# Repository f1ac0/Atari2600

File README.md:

# Atari2600
Inside the lot I bought to get my first C64 was also and Atari 2600. It was also listed as "Untested", and it was obviously salvaged from a flood considering the mud and rust that was inside the case. It came without any game or accessory.

While waiting for the system to dry after a complete clean and rust removal I found the useful projects below to help me start with this system I didn't know anything about.
- First I needed some game so I put together a ROM cartridge on a breadboard and created a PCB from it.
- Then not a single TV receiver I had could tune the video and audio signals correctly, but a BT848 PCTV PCI card. The mod by Eddy Foucault worked perfectly, I made my own version with CMS components and 5v only.
- At last I removed the regulator to power the console from a modern 5V power source.

In this repository are the PCBs I created or modified for my own needs.

# Disclaimer and Acknowledgements
This is a hobbyist project, it comes with no warranty and no support. Also remember that the 40 years old hardware may fail because of such expansions.

I publish my work under the CC-BY-NC-SA license, unless stated otherwise. Thanks to everyone who share their knowledge and creations.

# Useful links

## Cartridge
- https://github.com/sarweiler/a2k6-cart
- https://github.com/robinhedwards/UnoCart-2600
- https://github.com/DirtyHairy/UnoCart-2600/releases
- https://github.com/rglenn/unocart2600-pcb
- https://github.com/Al-Nafuur/United-Carts-of-Atari

## Video SECAM Atari 2600 to RGB SCART TV
- http://eddystoys.blogspot.com/2014/08/atari-2600.html

## Video SECAM to PAL
- https://forums.atariage.com/topic/245189-converting-a-secam-atari-2600-to-pal-or-ntsc/

## Video PAL/NTSC to composite
- https://www.arcticretro.com/2021/03/27/atari-2600-composite-video-mod/
- https://www.instructables.com/ATARI-2600-Video-Composite-mod/

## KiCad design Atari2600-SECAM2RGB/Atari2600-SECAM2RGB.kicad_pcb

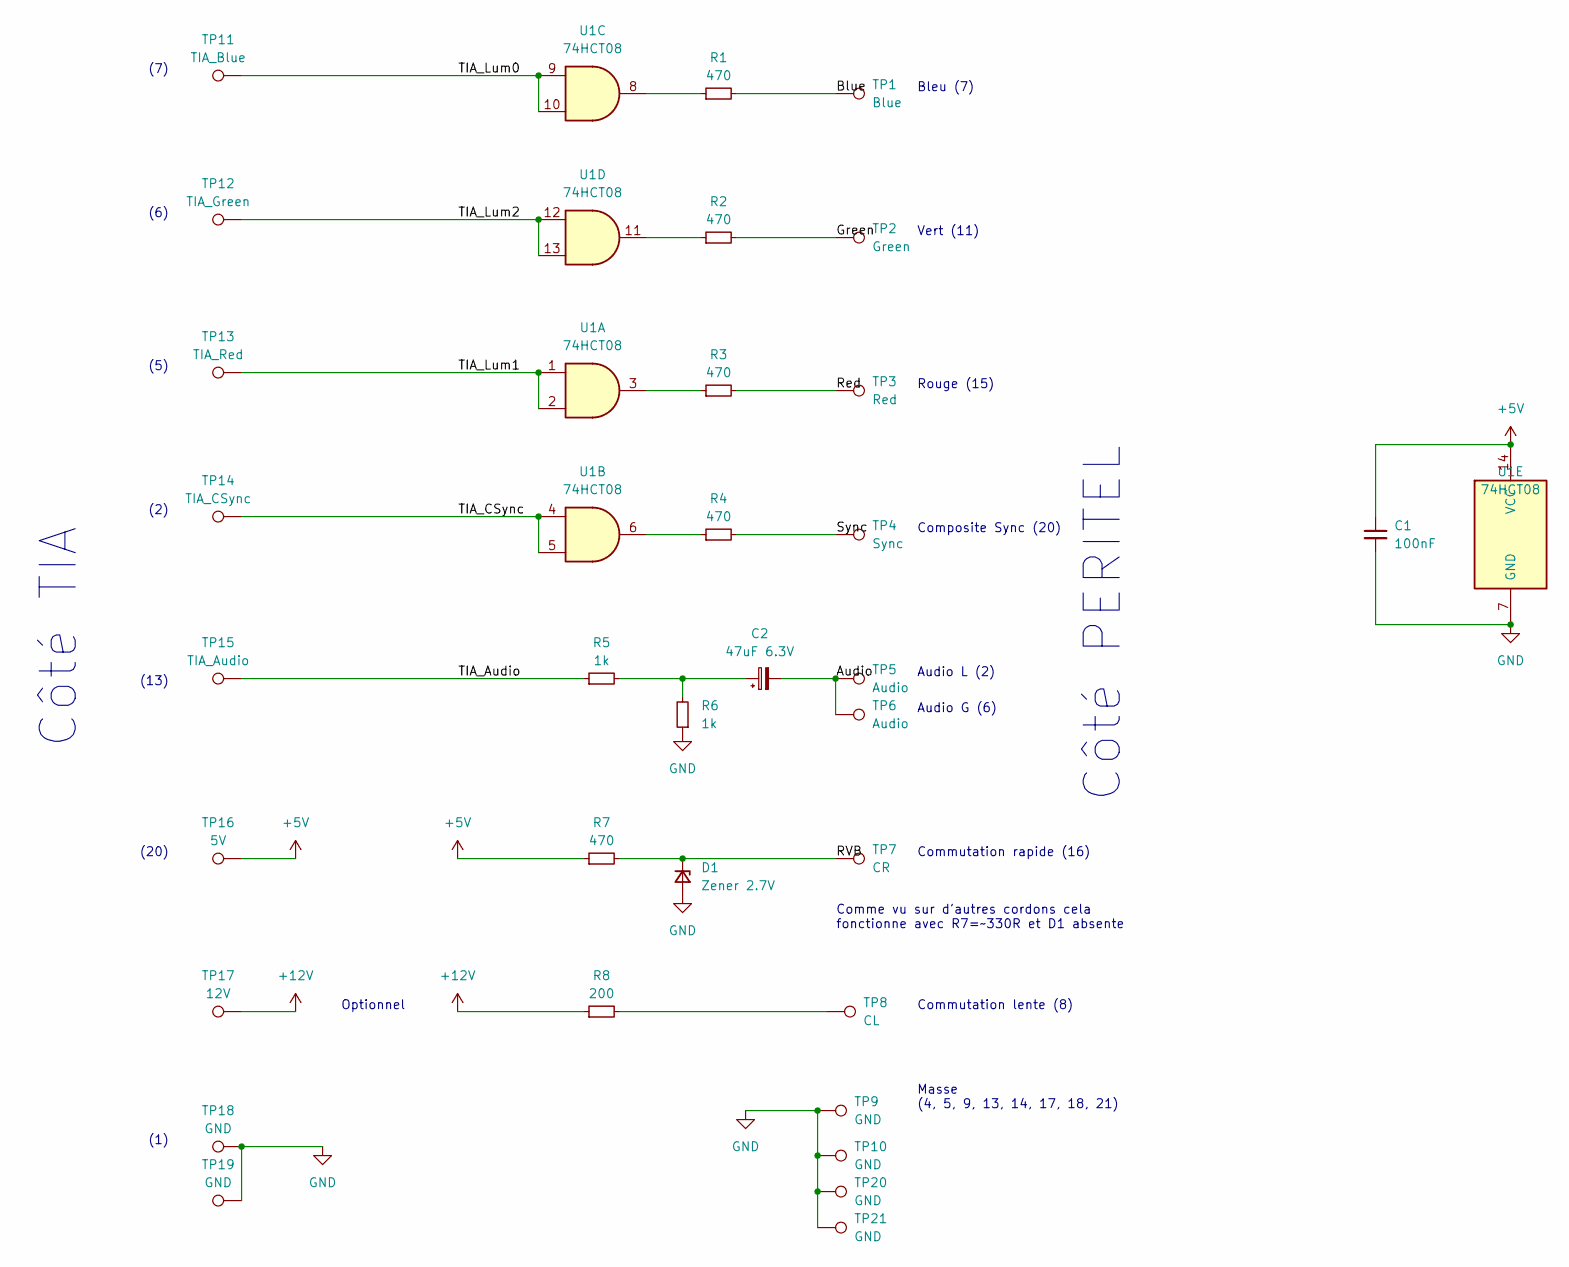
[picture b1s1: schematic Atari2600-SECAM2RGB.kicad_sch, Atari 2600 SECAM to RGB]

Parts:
C1: 100nF; C_0805_2012Metric
C2: 47uF 6.3V; CP_Elec_6.3x5.4
D1: Zener 2.7V; D_0805_2012Metric
R1, R2, R3, R4, R7: 470; R_0805_2012Metric
R5, R6: 1k; R_0805_2012Metric
R8: 200; R_0805_2012Metric
TP1: Blue; TestPoint_THTPad_D1.7mm_Drill1.0mm
TP2: Green; TestPoint_THTPad_D1.7mm_Drill1.0mm
TP3: Red; TestPoint_THTPad_D1.7mm_Drill1.0mm
TP4: Sync; TestPoint_THTPad_D1.7mm_Drill1.0mm
TP5, TP6: Audio; TestPoint_THTPad_D1.7mm_Drill1.0mm
TP7: CR; TestPoint_THTPad_D1.7mm_Drill1.0mm
TP8: CL; TestPoint_THTPad_D1.7mm_Drill1.0mm
TP9, TP10, TP18, TP19, TP20, TP21: GND; TestPoint_THTPad_D1.7mm_Drill1.0mm
TP11: TIA_Blue; TestPoint_THTPad_D1.7mm_Drill1.0mm
TP12: TIA_Green; TestPoint_THTPad_D1.7mm_Drill1.0mm
TP13: TIA_Red; TestPoint_THTPad_D1.7mm_Drill1.0mm
TP14: TIA_CSync; TestPoint_THTPad_D1.7mm_Drill1.0mm
TP15: TIA_Audio; TestPoint_THTPad_D1.7mm_Drill1.0mm
TP16: 5V; TestPoint_THTPad_D1.7mm_Drill1.0mm
TP17: 12V; TestPoint_THTPad_D1.7mm_Drill1.0mm
U1: 74HCT08; SO-14_3.9x8.65mm_P1.27mm

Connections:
+5V: C1.1, R7.1, TP16.1, U1.14 (VCC)
+12V: R8.1, TP17.1
/Audio: C2.2, TP5.1, TP6.1
/Blue: R1.2, TP1.1
/Green: R2.2, TP2.1
/RVB: D1.1 (K), R7.2, TP7.1
/Red: R3.2, TP3.1
/Sync: R4.2, TP4.1
/TIA_Audio: R5.1, TP15.1
/TIA_CSync: TP14.1, U1.4, U1.5
/TIA_Lum0: TP11.1, U1.9, U1.10
/TIA_Lum1: TP13.1, U1.1, U1.2
/TIA_Lum2: TP12.1, U1.12, U1.13
GND: C1.2, D1.2 (A), R6.1, TP9.1, TP10.1, TP18.1, TP19.1, TP20.1, TP21.1, U1.7 (GND)
unnamed: C2.1, R5.2, R6.2
unnamed: R1.1, U1.8
unnamed: R2.1, U1.11
unnamed: R3.1, U1.3
unnamed: R4.1, U1.6
unnamed: R8.2, TP8.1

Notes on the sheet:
Vert (11)
Rouge (15)
Composite Sync (20)
(7)
Côté PERITEL
Audio G (6)
Bleu (7)
(13)
(1)
(20)
Audio L (2)
Optionnel
Côté TIA
(6)
Comme vu sur d'autres cordons cela fonctionne avec R7=~330R et D1 absente
(2)
Commutation rapide (16)
Masse (4, 5, 9, 13, 14, 17, 18, 21)
(5)
Commutation lente (8)

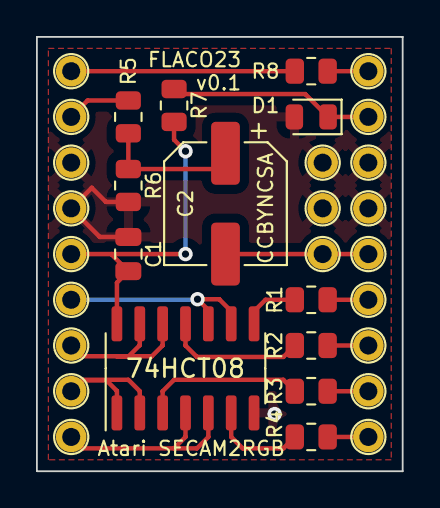
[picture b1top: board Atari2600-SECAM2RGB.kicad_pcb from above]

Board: 2 copper layers, 20.3 x 24.1 mm, 33 parts (0 on the bottom side), 20 nets.

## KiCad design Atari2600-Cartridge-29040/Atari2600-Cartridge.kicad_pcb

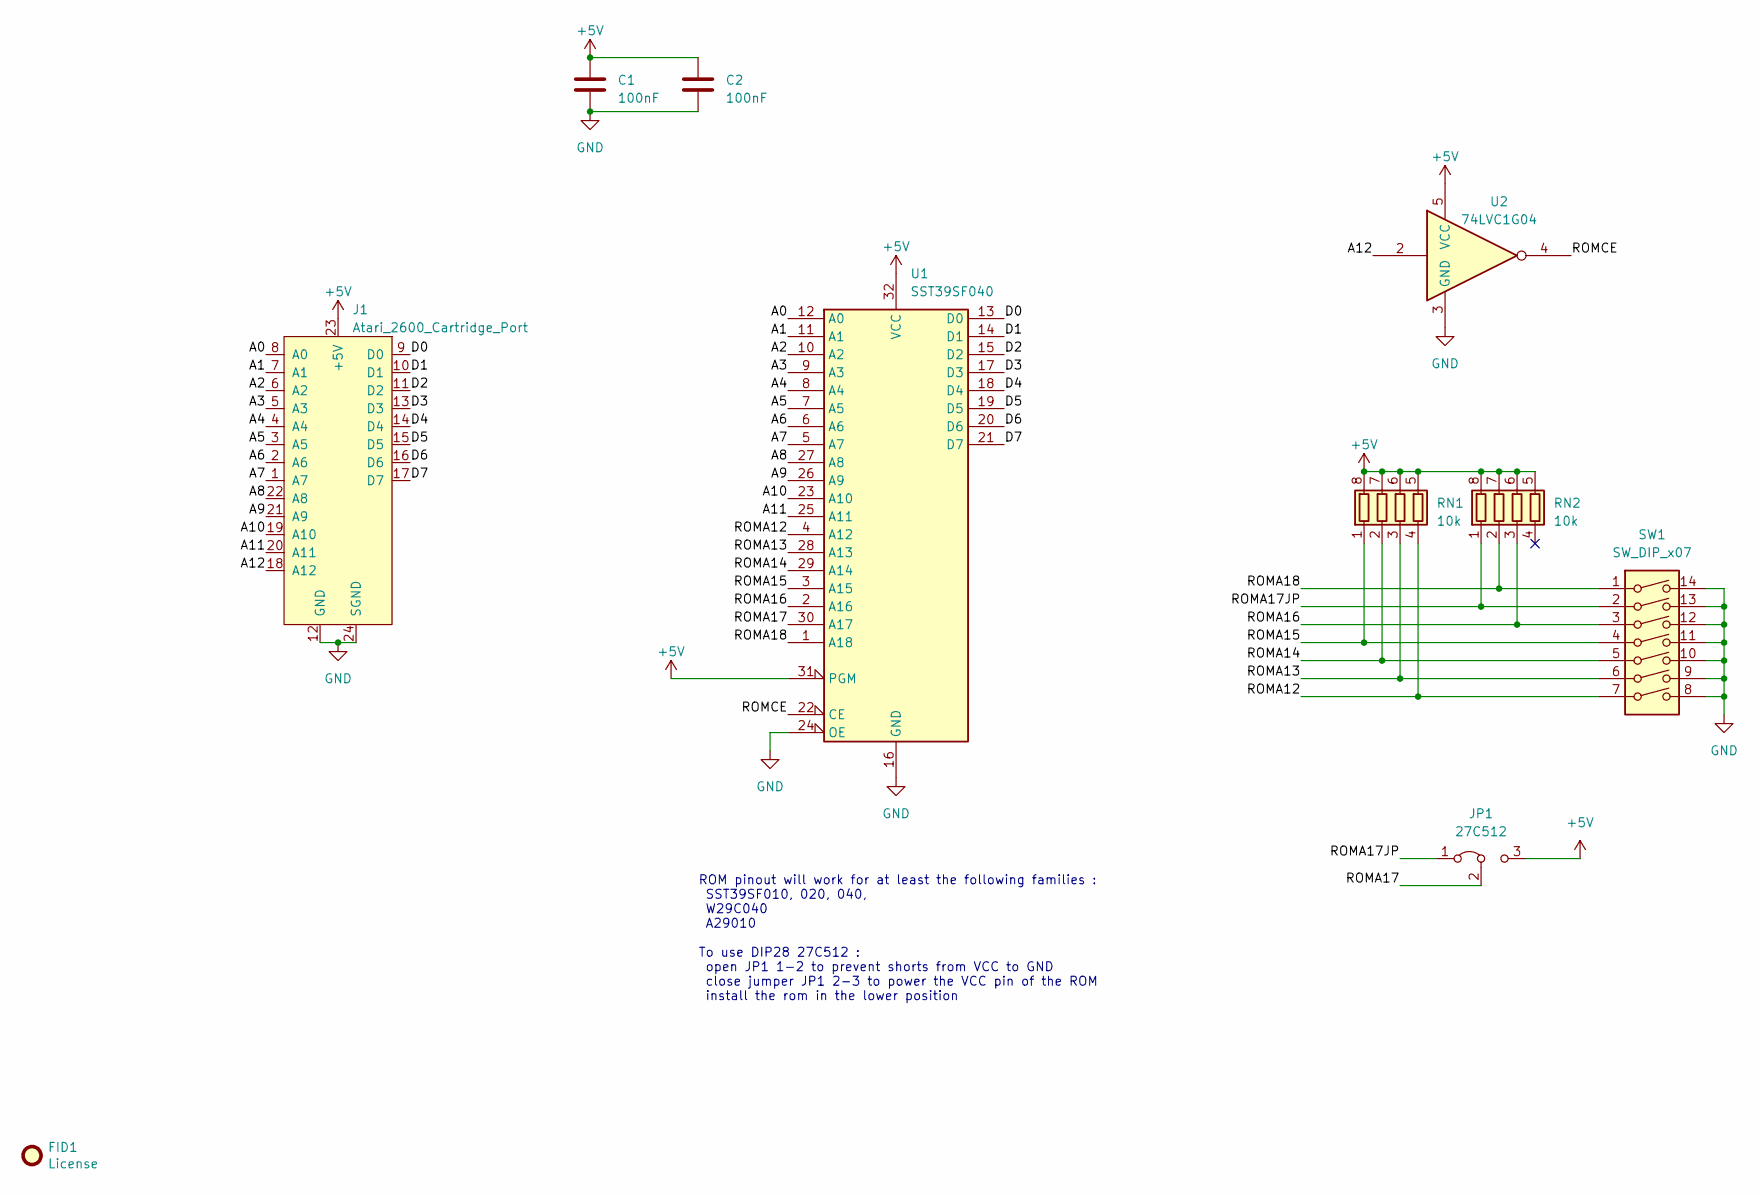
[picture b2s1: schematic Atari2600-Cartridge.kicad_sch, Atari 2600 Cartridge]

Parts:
C1, C2: 100nF; C_0805_2012Metric
FID1: License; CC_BY_NC_SA_square_silkscreen
J1: Atari_2600_Cartridge_Port; Atari2600_Cartridge_2x12_P2.54mm
JP1: 27C512; SolderJumper-3_P1.3mm_Bridged12_RoundedPad1.0x1.5mm
RN1, RN2: 10k; R_Array_Concave_4x0603
SW1: SW_DIP_x07; SW_DIP_SPSTx07_Slide_9.78x19.96mm_W7.62mm_P2.54mm
U1: SST39SF040; DIP-32_W15.24mm
U2: 74LVC1G04; SOT-23-5

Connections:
+5V: C1.1, C2.1, J1.23 (+5V), JP1.3 (B), RN1.5 (R4.2), RN1.6 (R3.2), RN1.7 (R2.2), RN1.8 (R1.2), RN2.5 (R4.2), RN2.6 (R3.2), RN2.7 (R2.2), RN2.8 (R1.2), U1.31 (PGM), U1.32 (VCC), U2.5 (VCC)
/A0: J1.8 (A0), U1.12 (A0)
/A1: J1.7 (A1), U1.11 (A1)
/A2: J1.6 (A2), U1.10 (A2)
/A3: J1.5 (A3), U1.9 (A3)
/A4: J1.4 (A4), U1.8 (A4)
/A5: J1.3 (A5), U1.7 (A5)
/A6: J1.2 (A6), U1.6 (A6)
/A7: J1.1 (A7), U1.5 (A7)
/A8: J1.22 (A8), U1.27 (A8)
/A9: J1.21 (A9), U1.26 (A9)
/A10: J1.19 (A10), U1.23 (A10)
/A11: J1.20 (A11), U1.25 (A11)
/A12: J1.18 (A12), U2.2
/D0: J1.9 (D0), U1.13 (D0)
/D1: J1.10 (D1), U1.14 (D1)
/D2: J1.11 (D2), U1.15 (D2)
/D3: J1.13 (D3), U1.17 (D3)
/D4: J1.14 (D4), U1.18 (D4)
/D5: J1.15 (D5), U1.19 (D5)
/D6: J1.16 (D6), U1.20 (D6)
/D7: J1.17 (D7), U1.21 (D7)
/ROMA12: RN1.4 (R4.1), SW1.7, U1.4 (A12)
/ROMA13: RN1.3 (R3.1), SW1.6, U1.28 (A13)
/ROMA14: RN1.2 (R2.1), SW1.5, U1.29 (A14)
/ROMA15: RN1.1 (R1.1), SW1.4, U1.3 (A15)
/ROMA16: RN2.3 (R3.1), SW1.3, U1.2 (A16)
/ROMA17: JP1.2 (C), U1.30 (A17)
/ROMA17JP: JP1.1 (A), RN2.1 (R1.1), SW1.2
/ROMA18: RN2.2 (R2.1), SW1.1, U1.1 (A18)
/ROMCE: U1.22 (CE), U2.4
GND: C1.2, C2.2, J1.12 (GND), J1.24 (SGND), SW1.8, SW1.9, SW1.10, SW1.11, SW1.12, SW1.13, SW1.14, U1.16 (GND), U1.24 (OE), U2.3 (GND)

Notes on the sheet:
ROM pinout will work for at least the following families : SST39SF010, 020, 040, W29C040 A29010 To use DIP28 27C512 : open JP1 1-2 to prevent shorts from VCC to GND close jumper JP1 2-3 to power the VCC pin of the ROM install the rom in the lower position

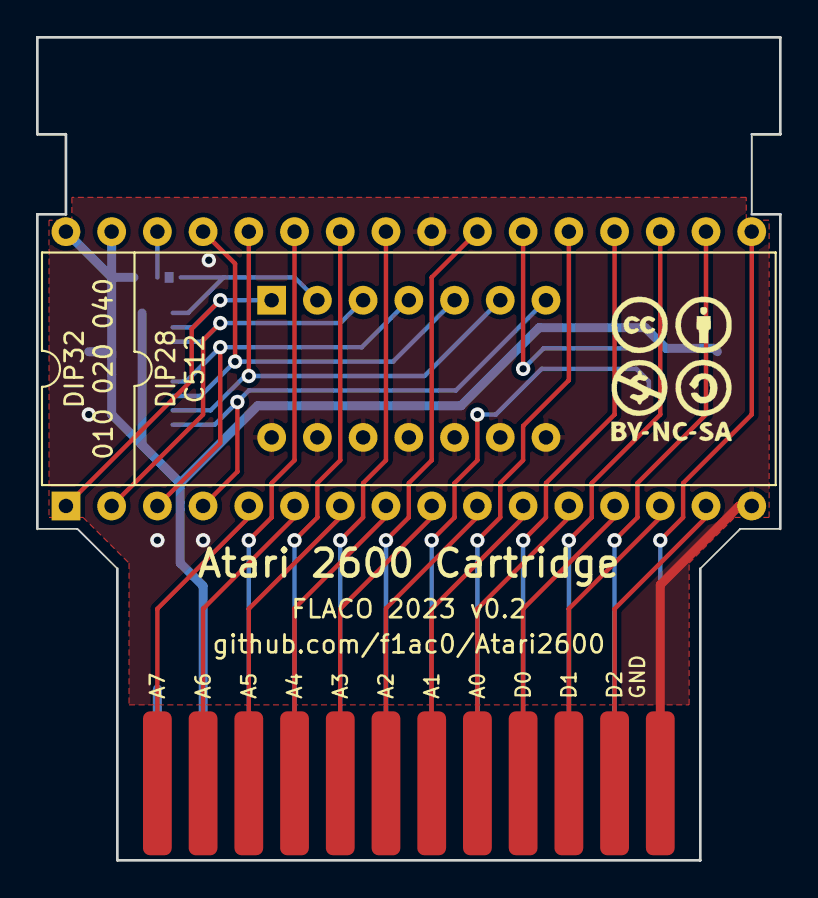
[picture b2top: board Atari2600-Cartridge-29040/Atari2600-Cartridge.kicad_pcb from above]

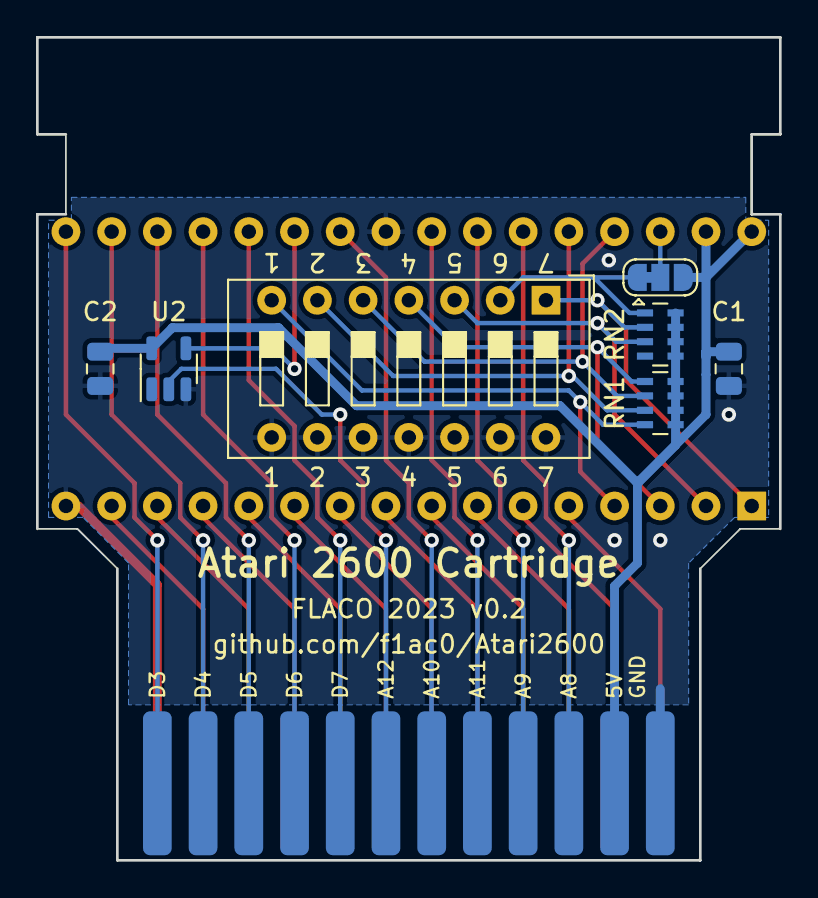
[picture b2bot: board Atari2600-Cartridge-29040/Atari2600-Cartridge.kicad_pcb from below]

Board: 2 copper layers, 41.3 x 45.7 mm, 10 parts (7 on the bottom side), 32 nets.

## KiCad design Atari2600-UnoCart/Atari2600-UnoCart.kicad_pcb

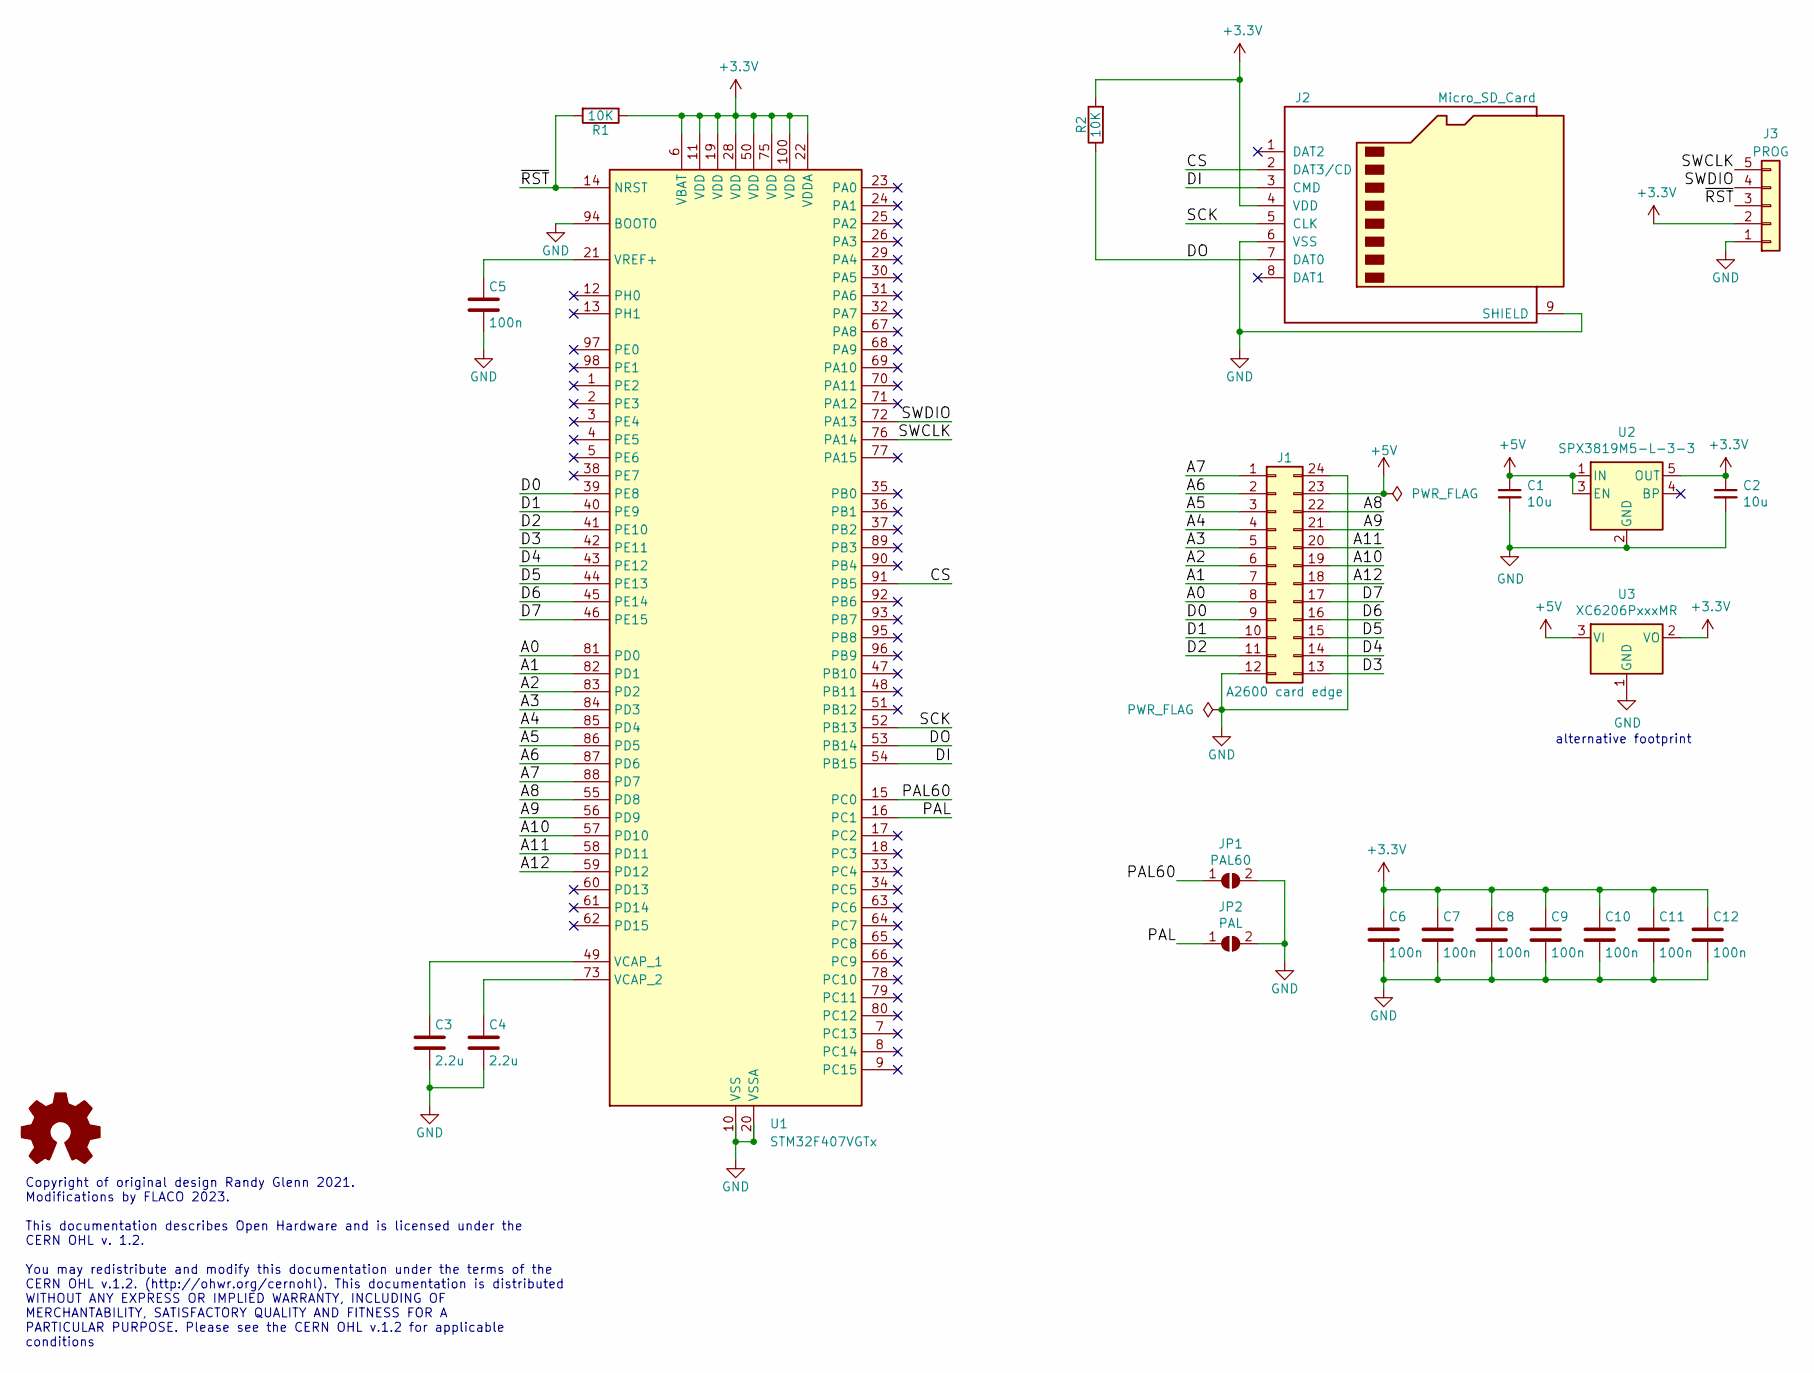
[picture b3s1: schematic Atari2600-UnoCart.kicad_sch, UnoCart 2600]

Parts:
C1, C2: 10u; C_0805_2012Metric
C3, C4: 2.2u; C_0805_2012Metric
C5, C6, C7, C8, C9, C10, C11, C12: 100n; C_0805_2012Metric
J1: A2600 card edge; Atari2600_Cartridge_2x12_P2.54mm
J2: Micro_SD_Card; TFP09-2-12B
J3: PROG; PinHeader_1x05_P2.54mm_Vertical
JP1: PAL60; SolderJumper-2_P1.3mm_Open_RoundedPad1.0x1.5mm
JP2: PAL; SolderJumper-2_P1.3mm_Open_RoundedPad1.0x1.5mm
R1, R2: 10K; R_0805_2012Metric
U1: STM32F407VGTx; LQFP-100_14x14mm_P0.5mm
U2: SPX3819M5-L-3-3; SOT-23-5
U3: XC6206PxxxMR; SOT-23

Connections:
+3.3V: C2.1, C6.1, C7.1, C8.1, C9.1, C10.1, C11.1, C12.1, J2.4 (VDD), J3.2, R1.1, R2.2, U1.6 (VBAT), U1.11 (VDD), U1.19 (VDD), U1.22 (VDDA), U1.28 (VDD), U1.50 (VDD), U1.75 (VDD), U1.100 (VDD), U2.5 (OUT), U3.2 (VO)
+5V: C1.1, J1.23, U2.1 (IN), U2.3 (EN), U3.3 (VI)
/A0: J1.8, U1.81 (PD0)
/A1: J1.7, U1.82 (PD1)
/A2: J1.6, U1.83 (PD2)
/A3: J1.5, U1.84 (PD3)
/A4: J1.4, U1.85 (PD4)
/A5: J1.3, U1.86 (PD5)
/A6: J1.2, U1.87 (PD6)
/A7: J1.1, U1.88 (PD7)
/A8: J1.22, U1.55 (PD8)
/A9: J1.21, U1.56 (PD9)
/A10: J1.19, U1.57 (PD10)
/A11: J1.20, U1.58 (PD11)
/A12: J1.18, U1.59 (PD12)
/CS: J2.2 (DAT3/CD), U1.91 (PB5)
/D0: J1.9, U1.39 (PE8)
/D1: J1.10, U1.40 (PE9)
/D2: J1.11, U1.41 (PE10)
/D3: J1.13, U1.42 (PE11)
/D4: J1.14, U1.43 (PE12)
/D5: J1.15, U1.44 (PE13)
/D6: J1.16, U1.45 (PE14)
/D7: J1.17, U1.46 (PE15)
/DI: J2.3 (CMD), U1.54 (PB15)
/DO: J2.7 (DAT0), R2.1, U1.53 (PB14)
/PAL: JP2.1 (A), U1.16 (PC1)
/PAL60: JP1.1 (A), U1.15 (PC0)
/SCK: J2.5 (CLK), U1.52 (PB13)
/SWCLK: J3.5, U1.76 (PA14)
/SWDIO: J3.4, U1.72 (PA13)
/~RST: J3.3, R1.2, U1.14 (NRST)
GND: C1.2, C2.2, C3.2, C4.2, C5.2, C6.2, C7.2, C8.2, C9.2, C10.2, C11.2, C12.2, J1.12, J1.24, J2.6 (VSS), J2.9 (SHIELD), J3.1, JP1.2 (B), JP2.2 (B), U1.10 (VSS), U1.20 (VSSA), U1.27 (VSS), U1.74 (VSS), U1.94 (BOOT0), U1.99 (VSS), U2.2 (GND), U3.1 (GND)
unnamed: C3.1, U1.49 (VCAP_1)
unnamed: C4.1, U1.73 (VCAP_2)
unnamed: C5.1, U1.21 (VREF+)

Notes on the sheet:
Copyright of original design Randy Glenn 2021. Modifications by FLACO 2023. This documentation describes Open Hardware and is licensed under the CERN OHL v. 1.2. You may redistribute and modify this documentation under the terms of the CERN OHL v.1.2. (http://ohwr.org/cernohl). This documentation i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
alternative footprint

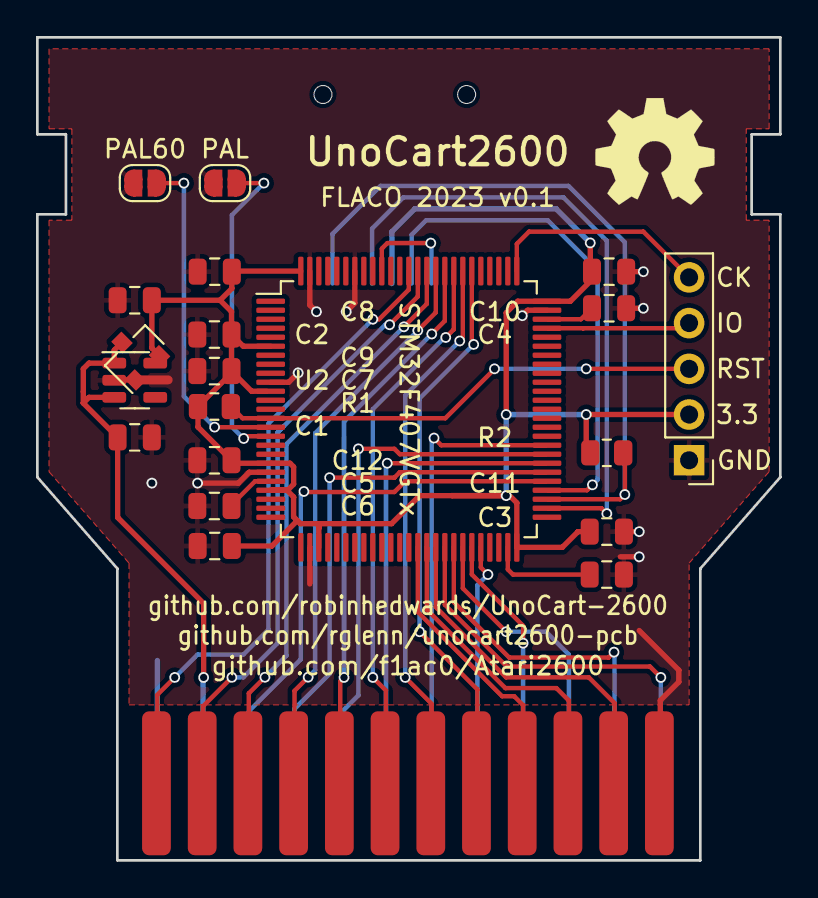
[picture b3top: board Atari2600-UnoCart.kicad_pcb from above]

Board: 2 copper layers, 41.3 x 45.7 mm, 22 parts (1 on the bottom side), 36 nets.

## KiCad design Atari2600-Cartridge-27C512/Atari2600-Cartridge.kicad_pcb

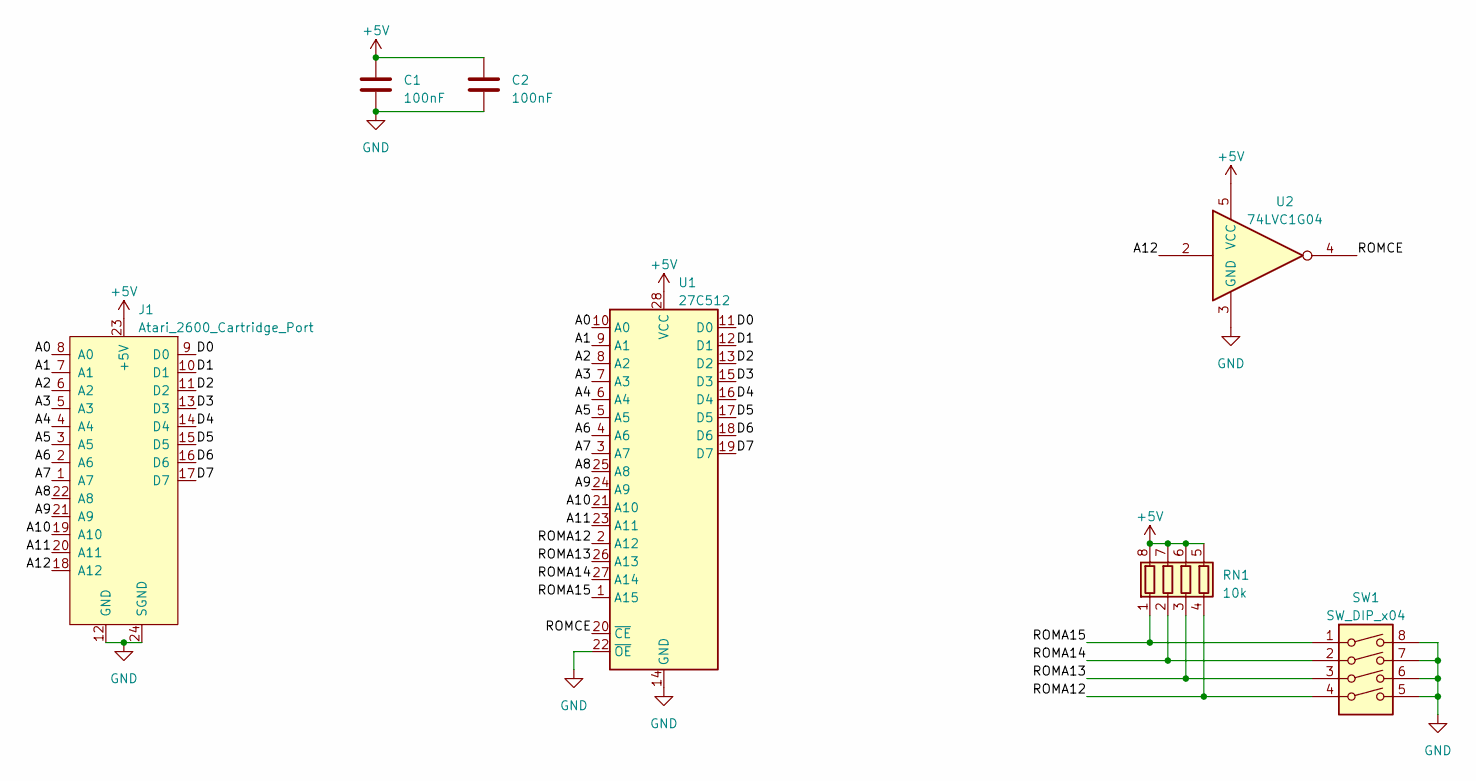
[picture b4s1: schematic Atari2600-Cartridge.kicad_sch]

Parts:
C1, C2: 100nF; C_0805_2012Metric
J1: Atari_2600_Cartridge_Port; Atari2600_Cartridge_2x12_P2.54mm
RN1: 10k; R_Array_Concave_4x0603
SW1: SW_DIP_x04; SW_DIP_SPSTx04_Slide_9.78x12.34mm_W7.62mm_P2.54mm
U1: 27C512; DIP-28_W15.24mm
U2: 74LVC1G04; SOT-23-5

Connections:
+5V: C1.1, C2.1, J1.23 (+5V), RN1.5 (R4.2), RN1.6 (R3.2), RN1.7 (R2.2), RN1.8 (R1.2), U1.28 (VCC), U2.5 (VCC)
/A0: J1.8 (A0), U1.10 (A0)
/A1: J1.7 (A1), U1.9 (A1)
/A2: J1.6 (A2), U1.8 (A2)
/A3: J1.5 (A3), U1.7 (A3)
/A4: J1.4 (A4), U1.6 (A4)
/A5: J1.3 (A5), U1.5 (A5)
/A6: J1.2 (A6), U1.4 (A6)
/A7: J1.1 (A7), U1.3 (A7)
/A8: J1.22 (A8), U1.25 (A8)
/A9: J1.21 (A9), U1.24 (A9)
/A10: J1.19 (A10), U1.21 (A10)
/A11: J1.20 (A11), U1.23 (A11)
/A12: J1.18 (A12), U2.2
/D0: J1.9 (D0), U1.11 (D0)
/D1: J1.10 (D1), U1.12 (D1)
/D2: J1.11 (D2), U1.13 (D2)
/D3: J1.13 (D3), U1.15 (D3)
/D4: J1.14 (D4), U1.16 (D4)
/D5: J1.15 (D5), U1.17 (D5)
/D6: J1.16 (D6), U1.18 (D6)
/D7: J1.17 (D7), U1.19 (D7)
/ROMA12: RN1.4 (R4.1), SW1.4, U1.2 (A12)
/ROMA13: RN1.3 (R3.1), SW1.3, U1.26 (A13)
/ROMA14: RN1.2 (R2.1), SW1.2, U1.27 (A14)
/ROMA15: RN1.1 (R1.1), SW1.1, U1.1 (A15)
/ROMCE: U1.20 (~CE), U2.4
GND: C1.2, C2.2, J1.12 (GND), J1.24 (SGND), SW1.5, SW1.6, SW1.7, SW1.8, U1.14 (GND), U1.22 (~OE), U2.3 (GND)

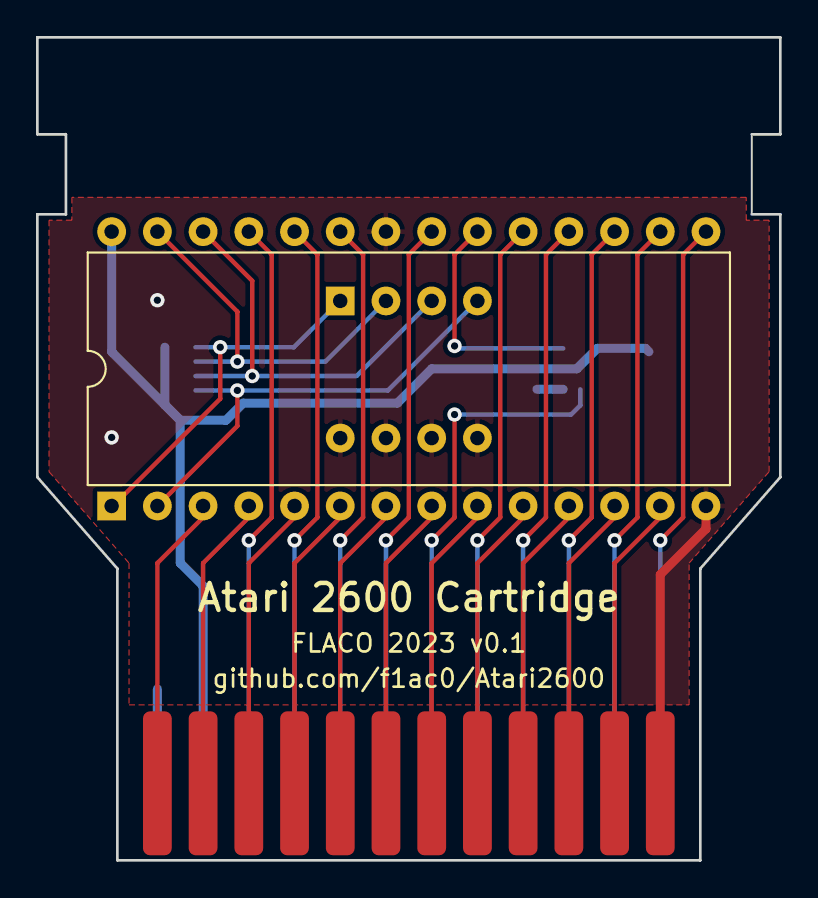
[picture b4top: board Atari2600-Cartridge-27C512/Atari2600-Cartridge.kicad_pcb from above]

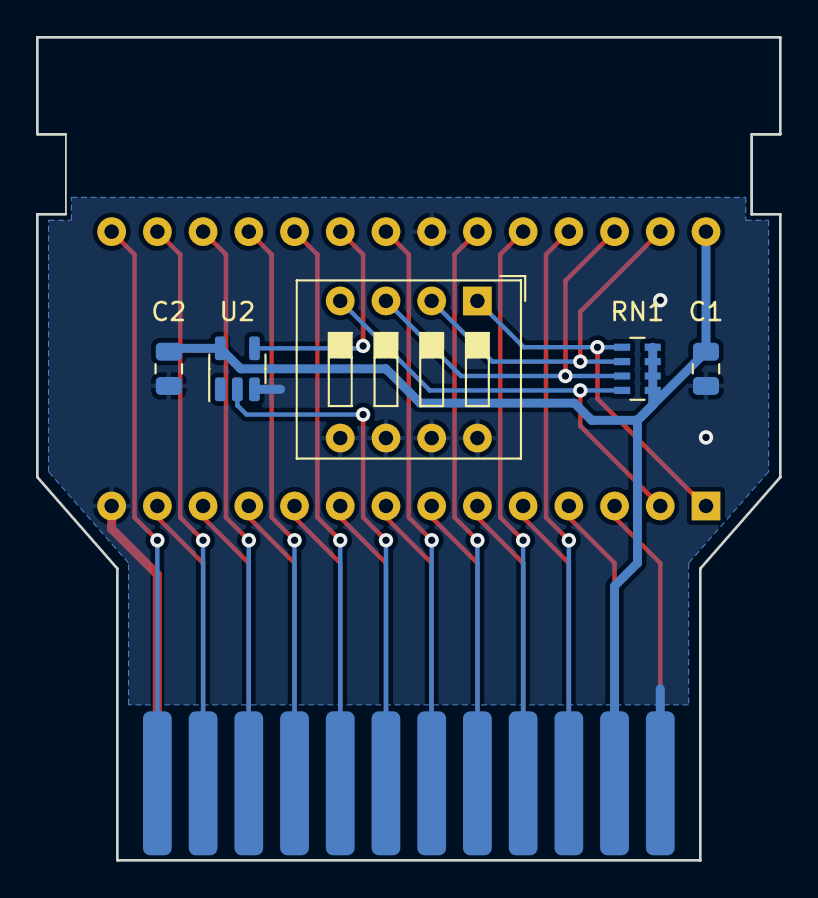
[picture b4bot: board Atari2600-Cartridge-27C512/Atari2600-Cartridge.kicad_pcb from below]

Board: 2 copper layers, 41.3 x 45.7 mm, 7 parts (5 on the bottom side), 28 nets.

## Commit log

2023-03-06 Respository init with KiCAD files, Readme and License
2023-05-30 Addition of Atari2600-Cartridge-29040 to support DIP32 EEPROMs. Addition of Interactive Boms.
2024-01-15 Addition of Atari2600-SECAM2RGB ; update license of Atari2600-UnoCart and README.

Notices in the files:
Atari2600-SECAM2RGB/Atari2600-SECAM2RGB.kicad_pcb:
FLACO 2023, CC-BY-NC-SA
